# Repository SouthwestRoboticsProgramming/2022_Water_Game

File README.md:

# 2022_Water_Game
 2022 water game confirmed!

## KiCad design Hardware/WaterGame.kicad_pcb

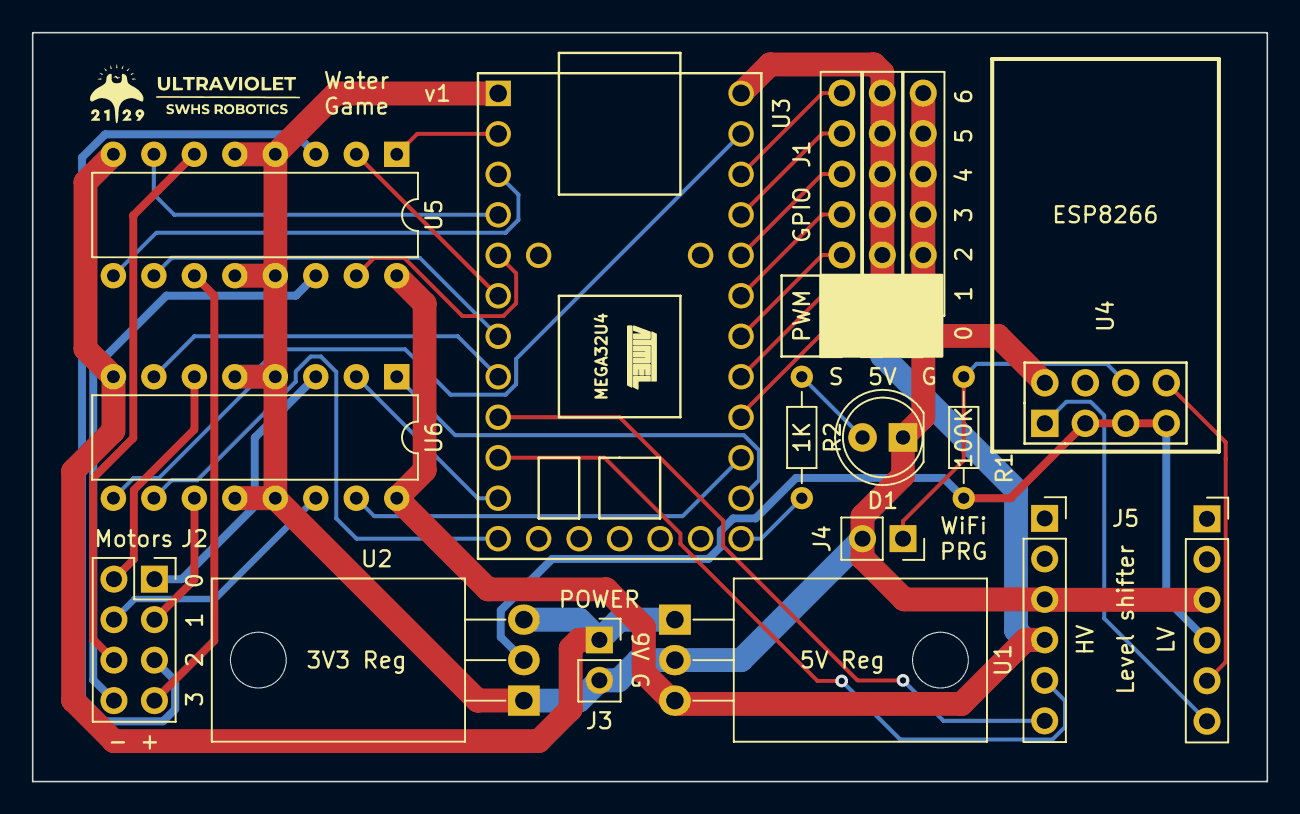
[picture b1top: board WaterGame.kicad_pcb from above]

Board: 2 copper layers, 77.5 x 47.0 mm, 17 parts (0 on the bottom side), 38 nets.

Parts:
D1: LED; LED_D5.0mm
J1A1, J1B1, J1C1: Conn_01x07; PinSocket_1x07_P2.54mm_Vertical
J2: Conn_02x04_Odd_Even; PinSocket_2x04_P2.54mm_Vertical
J3, J4: Conn_01x02; PinSocket_1x02_P2.54mm_Vertical
J5A1, J5A2: Conn_01x06; PinSocket_1x06_P2.54mm_Vertical
R1, R2: R; R_Axial_DIN0204_L3.6mm_D1.6mm_P7.62mm_Horizontal
U1: LM7805_TO220; TO-220-3_Horizontal_TabDown
U2: LD33V; TO-220-3_Horizontal_TabDown
U3: Teensy2.0_(Arduino); Teensy2.0
U4: ESP-01v090; ESP-01
U5, U6: L293D; DIP-16_W7.62mm

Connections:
unnamed: J1A1.1, U3.21 (14_A7_PWM)
unnamed: J1A1.2, U3.22 (15_A6_PWM)
unnamed: J1A1.3, U3.23 (16_A5)
unnamed: J1A1.4, U3.24 (17_A4)
unnamed: J1A1.5, U3.25 (18_A3)
unnamed: J1A1.6, U3.26 (19_A2)
unnamed: J1A1.7, U3.27 (20_A1)
unnamed: J1B1.1, J1B1.2, J1B1.3, J1B1.4, J1B1.5, J1B1.6, J1B1.7, J5A1.4, U1.3 (VO), U3.29 (+5V), U5.16 (VCC1), U6.16 (VCC1)
unnamed: D1.1 (K), J1C1.1, J1C1.2, J1C1.3, J1C1.4, J1C1.5, J1C1.6, J1C1.7, J3.2, J4.2, J5A1.3, J5A2.3, U1.2 (GND), U2.1 (VI), U3.1 (GND), U4.2 (GND), U5.4 (GND), U5.5 (GND), U5.12 (GND), U5.13 (GND), U6.4 (GND), U6.5 (GND), U6.12 (GND), U6.13 (GND)
unnamed: J2.5, U5.3 (1Y)
unnamed: J2.7, U5.11 (3Y)
unnamed: J2.8, U5.14 (4Y)
unnamed: J3.1, U1.1 (VI), U2.3 (VO), U5.8 (VCC2), U6.8 (VCC2)
unnamed: J4.1, R1.1, U4.6 (GPIO0)
unnamed: J5A1.5, U3.10 (8_INT3_TX)
unnamed: J5A1.6, U3.9 (7_INT2_RX)
unnamed: J5A2.4, R1.2, U2.2 (GND), U4.3 (CH_PD), U4.5 (RST), U4.7 (VCC)
unnamed: J5A2.5, U4.8 (URXD)
unnamed: J5A2.6, U4.1 (UTXD)
unnamed: D1.2 (A), R2.1
unnamed: U3.2 (0), U5.1 (EN1,2)
unnamed: U3.3 (1), U5.9 (EN3,4)
unnamed: U3.4 (2), U5.7 (2A)
unnamed: U3.5 (3), U5.15 (4A)
unnamed: U3.6 (4_PWM), U5.2 (1A)
unnamed: U3.7 (5_INT0_PWM), U5.10 (3A)
unnamed: U3.8 (6_INT1), U6.7 (2A)
unnamed: U3.11 (9_PWM), U6.2 (1A)
unnamed: U3.12 (10_PWM), U6.10 (3A)
unnamed: R2.2, U3.18 (11_A10_LED)
unnamed: U3.19 (12_A9_PWM), U6.1 (EN1,2)
unnamed: U3.20 (13_A8), U6.15 (4A)
unnamed: U3.28 (21_A0), U6.9 (EN3,4)
unnamed: J2.6, U5.6 (2Y)
unnamed: J2.1, U6.3 (1Y)
unnamed: J2.2, U6.6 (2Y)
unnamed: J2.3, U6.11 (3Y)
unnamed: J2.4, U6.14 (4Y)

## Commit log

2022-04-27 Add empty Arduino project
2022-04-27 Add motor control
2022-04-27 Add GPIO
2022-04-28 Use INPUT_PULLUP pinMode when reading GPIO
2022-04-28 Pre-create and cache motors and GPIO
2022-04-28 Split waterlib into multiple files
2022-05-03 Rewrite WaterLib
2022-05-03 Add networking test
2022-05-05 Driver station + make servo work
2022-05-07 Real networking
2022-05-10 Basic input device manager with keyboard input
2022-05-11 Send controller data to robot
2022-05-11 Hot-swappable controllers + basic steering example
2022-05-14 Add enable and disable controls
2022-05-14 Save keyboard key mappings
2022-05-14 Disable robot when closing driver station
2022-05-14 Prevent H-bridge shoot-through when switching motor direction from reverse to forward
2022-05-14 Reduce load on H-bridge catch diodes
2022-05-27 Add serial passthrough to program the ESP8266 WIFI module
2022-09-17 DriverStation: Add networked connection
2022-09-17 Firmware: Networked control
2022-09-17 Hardware: Schematic and PCB initial layout
2022-09-17 Hardware: Final PCB
2022-09-17 Add notes
2022-09-17 Hardware: Widened high-current traces
2022-09-17 Hardware: Generate gerber files
2022-09-17 Hardware: Fix ESP8266 program resistor pullup
2022-09-20 Hardware: Add dedicated status LED
2022-09-29 Hardware: Add more silkscreen labels
2022-09-29 Hardware: Commit unsaved changes
2022-09-30 Hardware: Make power traces wider
